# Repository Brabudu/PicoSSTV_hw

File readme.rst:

Case and PCB for PICO sstv project
==========================================

Here the firmware:
------------------

+ Original from Jon Dawson:
LCD TFT without touch.
You must connect 4 buttons via J3
<https://github.com/dawsonjon/PicoSSTV/tree/encoder>

+ Touch version from Franciscu Capuzzi IS0JSV :
<https://github.com/Brabudu/PicoSSTV>

--------------------

.. image::  images/case.jpg

--------------------

.. image::  images/top.jpg
.. image::  images/bottom.jpg
--------------------

.. image::  images/assembly.jpg
.. image::  images/all.jpg

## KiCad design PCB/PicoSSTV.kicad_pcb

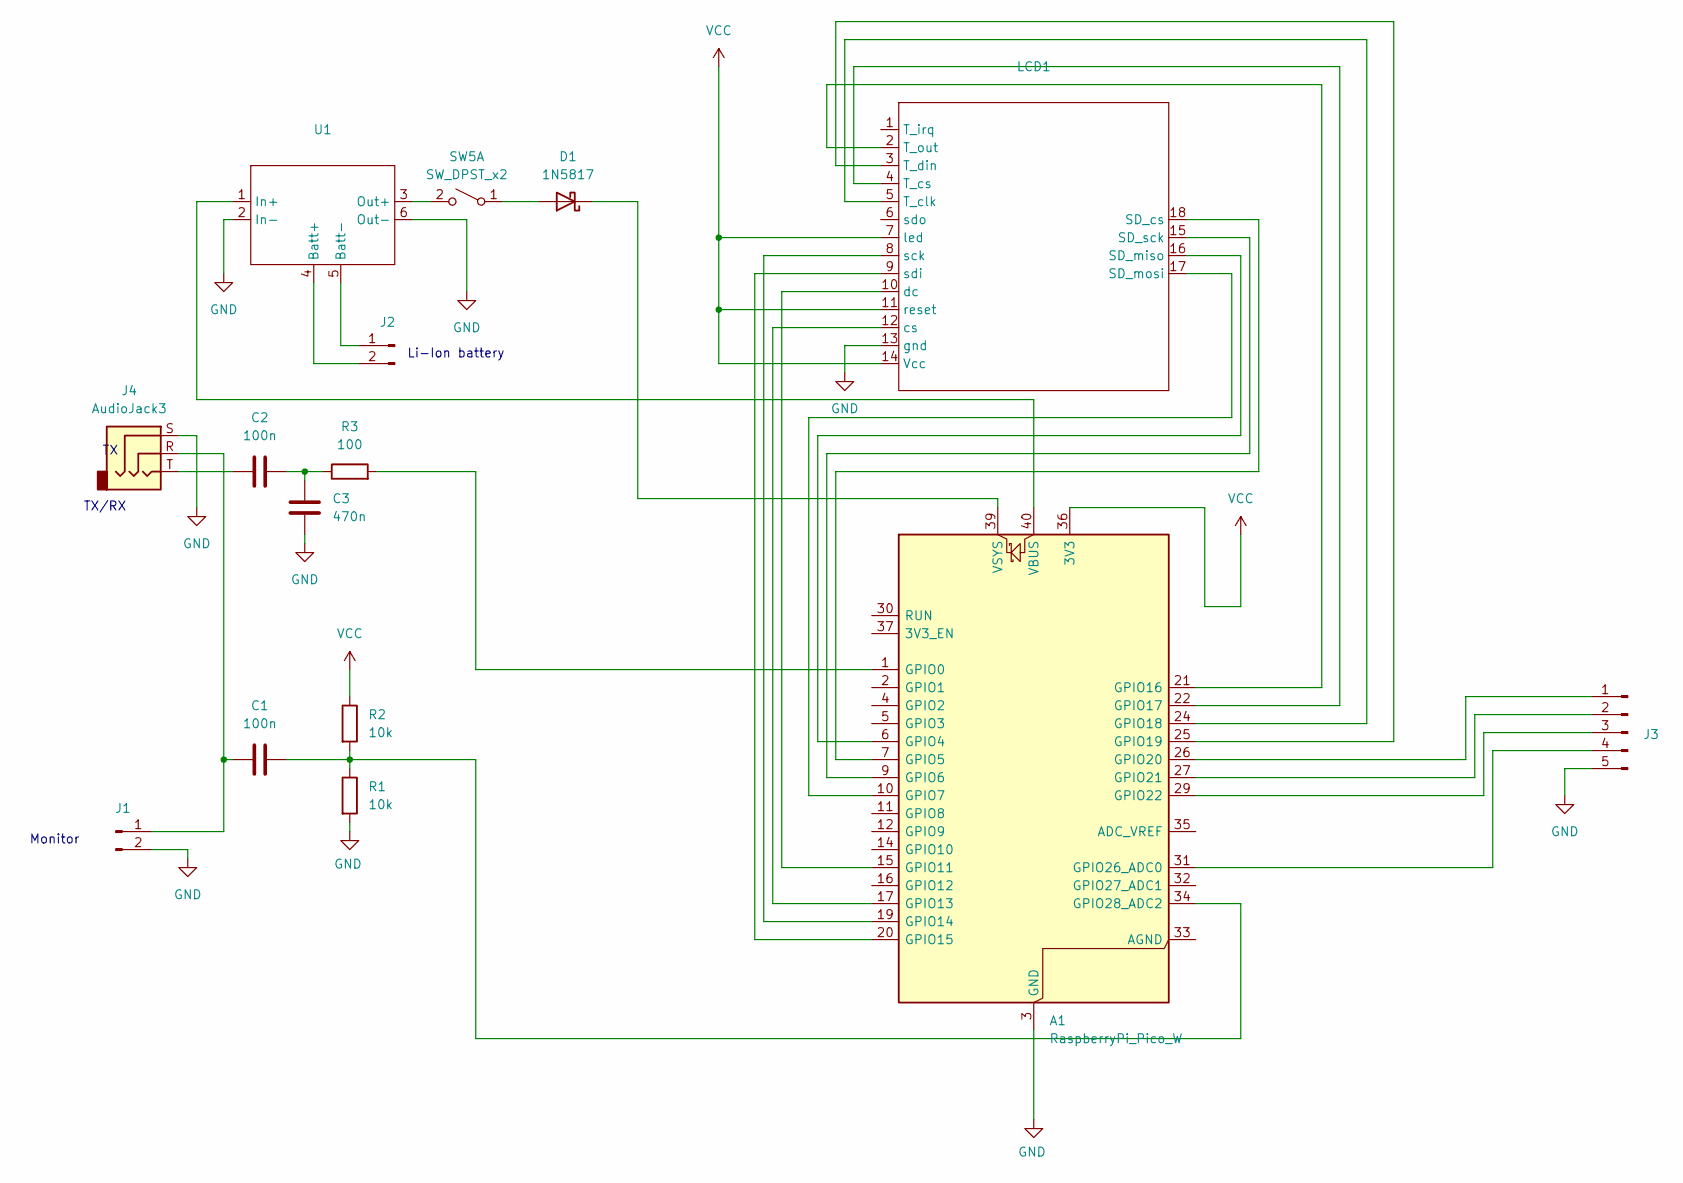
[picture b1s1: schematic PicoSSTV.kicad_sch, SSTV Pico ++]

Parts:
A1: RaspberryPi_Pico_W; RaspberryPi_Pico_Common_Unspecified
C1, C2: 100n; C_Rect_L7.0mm_W2.0mm_P5.00mm
C3: 470n; C_Rect_L7.0mm_W2.0mm_P5.00mm
D1: 1N5817; D_DO-41_SOD81_P10.16mm_Horizontal
J1: Conn_01x02_Pin; PinHeader_1x02_P2.00mm_Vertical
J2: Conn_01x02_Pin; SolderWire-0.15sqmm_1x02_P4mm_D0.5mm_OD1.5mm
J3: Conn_01x05_Pin; PinHeader_1x05_P2.54mm_Vertical
J4: AudioJack3; Jack_3.5mm_CUI_SJ1-3513N_Horizontal
LCD1: lcd_touch_3_2
R1, R2: 10k; R_Axial_DIN0207_L6.3mm_D2.5mm_P10.16mm_Horizontal
R3: 100; R_Axial_DIN0207_L6.3mm_D2.5mm_P10.16mm_Horizontal
SW5: SW_DPST_x2; SW_Slide_SPDT_Angled_CK_OS102011MA1Q
U1: LiIon_module

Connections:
GND: A1.3 (GND), A1.8 (GND), A1.13 (GND), A1.18 (GND), A1.23 (GND), A1.28 (GND), A1.38 (GND), C3.1, J1.2, J3.5, J4.S, LCD1.13 (gnd), R1.2, U1.2 (In-), U1.6 (Out-)
unnamed: A1.1 (GPIO0), R3.2
unnamed: A1.6 (GPIO4), LCD1.16 (SD_miso)
unnamed: A1.7 (GPIO5), LCD1.18 (SD_cs)
unnamed: A1.9 (GPIO6), LCD1.15 (SD_sck)
unnamed: A1.10 (GPIO7), LCD1.17 (SD_mosi)
unnamed: A1.15 (GPIO11), LCD1.10 (dc)
unnamed: A1.17 (GPIO13), LCD1.12 (cs)
unnamed: A1.19 (GPIO14), LCD1.8 (sck)
unnamed: A1.20 (GPIO15), LCD1.9 (sdi)
unnamed: A1.21 (GPIO16), LCD1.2 (T_out)
unnamed: A1.22 (GPIO17), LCD1.4 (T_cs)
unnamed: A1.24 (GPIO18), LCD1.5 (T_clk)
unnamed: A1.25 (GPIO19), LCD1.3 (T_din)
unnamed: A1.26 (GPIO20), J3.1
unnamed: A1.27 (GPIO21), J3.2
unnamed: A1.29 (GPIO22), J3.3
unnamed: A1.31 (GPIO26_ADC0), J3.4
unnamed: A1.34 (GPIO28_ADC2), C1.2, R1.1, R2.2
unnamed: A1.40 (VBUS), U1.1 (In+)
unnamed: A1.39 (VSYS), D1.1 (K)
unnamed: C2.1, J4.T
unnamed: C2.2, C3.2, R3.1
unnamed 23: D1.2 (A), SW5.1 (A); also elsewhere on the board
unnamed: C1.1, J1.1, J4.R
unnamed: J2.1, U1.5 (Batt-)
unnamed: J2.2, U1.4 (Batt+)
unnamed 27: SW5.2 (B), U1.3 (Out+); also elsewhere on the board
VCC: A1.36 (3V3), LCD1.7 (led), LCD1.11 (reset), LCD1.14 (Vcc), R2.1

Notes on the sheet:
Li-Ion battery
Monitor
TX/RX

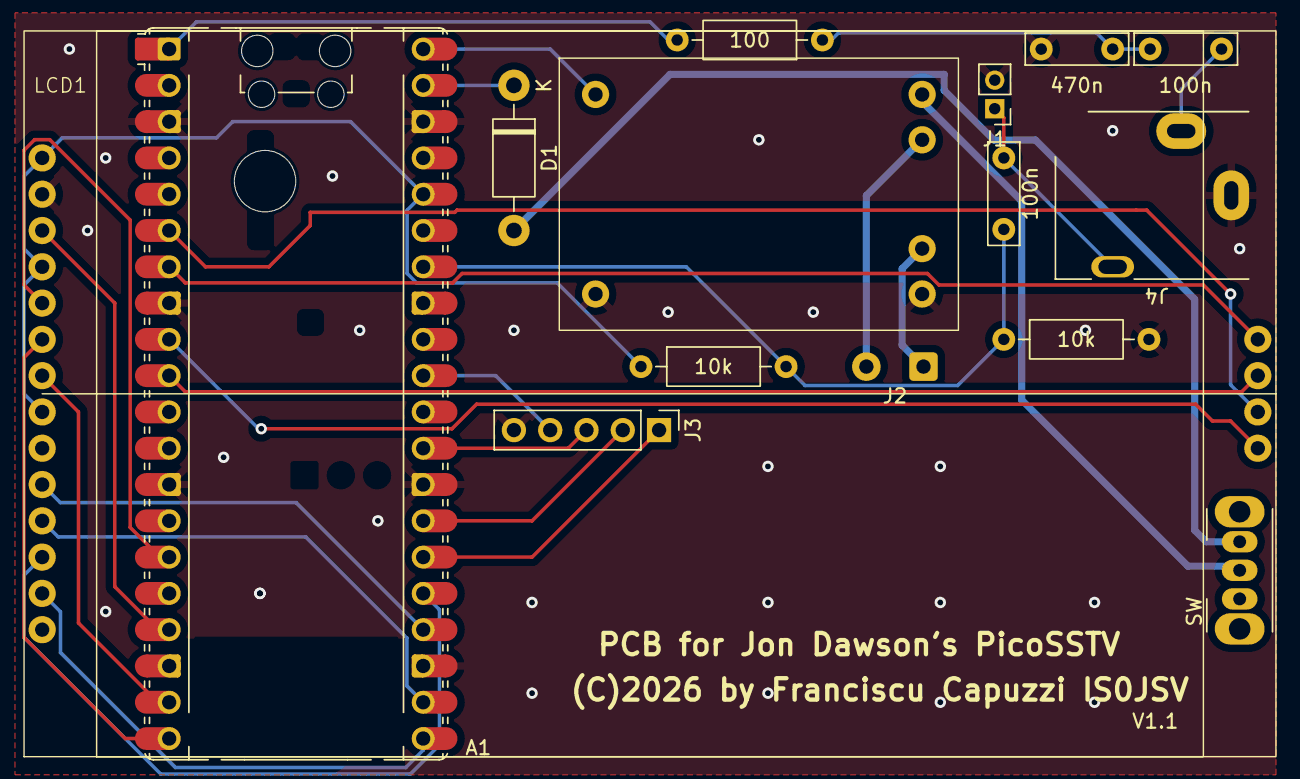
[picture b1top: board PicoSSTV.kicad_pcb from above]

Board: 2 copper layers, 15 parts (0 on the bottom side), 29 nets.

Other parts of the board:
SW: SW_DPST_x2; SW_Slide_SPDT_Angled_CK_OS102011MA1Q

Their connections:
unnamed 23: SW.1 (A); also elsewhere on the board
unnamed 27: SW.2 (B); also elsewhere on the board

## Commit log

2026-04-08 First upload

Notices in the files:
PCB/PicoSSTV.kicad_pcb:
(C)2026 by Franciscu Capuzzi IS0JSV
